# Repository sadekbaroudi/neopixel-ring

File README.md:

# fingerpunch neopixel ring

Two rings, seprated by breakaway tabs (mouse bites)

You can use it as one large ring, or break them apart for two smaller rings

## fabrication

This is set up to use at JLCPCB. You can fab with PCBA.

All the necessary files are in the pcb/production directory in this repository.

## images

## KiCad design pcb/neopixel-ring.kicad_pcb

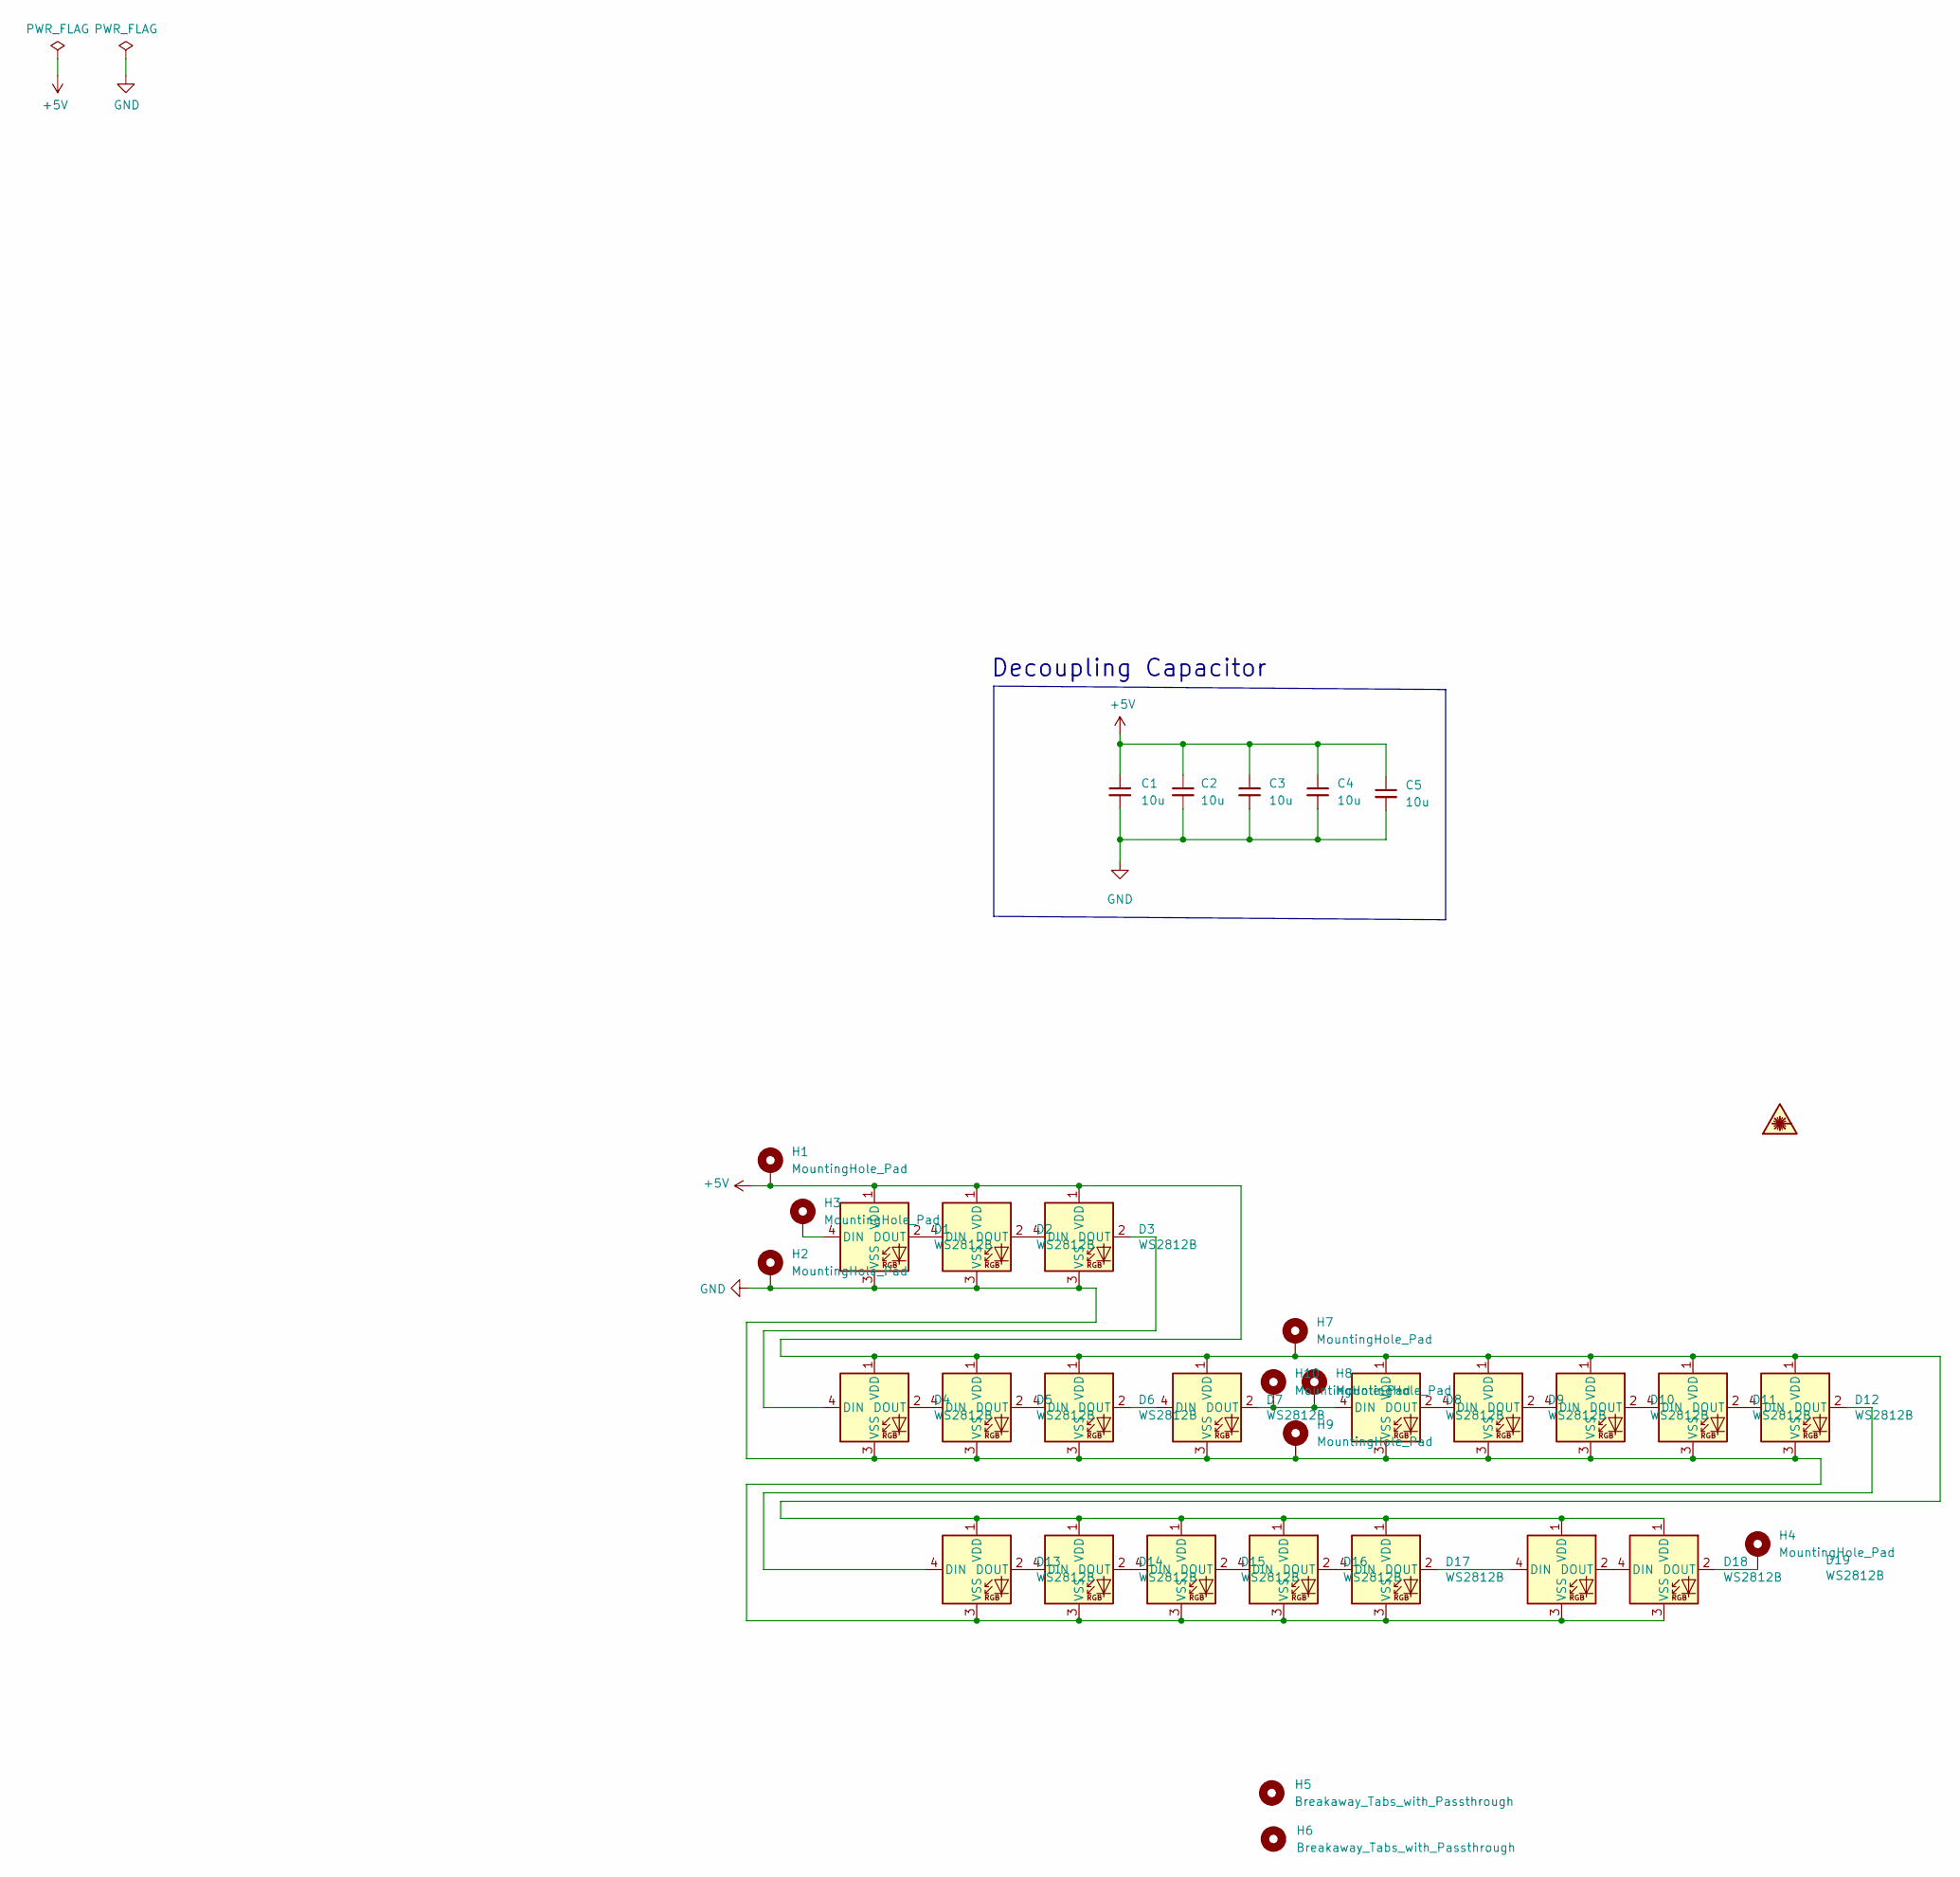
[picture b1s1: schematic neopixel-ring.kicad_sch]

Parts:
C1, C2, C3, C4, C5: 10u; C_0402_1005Metric; LCSC C2846677
D1, D2, D3, D4, D5, D6, D7, D8, D9, D10, D11, D12, D13, D14, D15, D16, D17, D18, D19: WS2812B; MPN WS2812B-B/W; LCSC C2761795
H1, H2, H3, H4, H7, H8, H9, H10: MountingHole_Pad; Pin_D0.7mm_L6.5mm_W1.8mm_FlatFork
H5, H6: Breakaway_Tabs_with_Passthrough

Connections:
+5V: C1.1, C2.1, C3.1, C4.1, C5.1, D1.1 (VDD), D2.1 (VDD), D3.1 (VDD), D4.1 (VDD), D5.1 (VDD), D6.1 (VDD), D7.1 (VDD), D8.1 (VDD), D9.1 (VDD), D10.1 (VDD), D11.1 (VDD), D12.1 (VDD), D13.1 (VDD), D14.1 (VDD), D15.1 (VDD), D16.1 (VDD), D17.1 (VDD), D18.1 (VDD), D19.1 (VDD), H1.1, H7.1
GND: C1.2, C2.2, C3.2, C4.2, C5.2, D1.3 (VSS), D2.3 (VSS), D3.3 (VSS), D4.3 (VSS), D5.3 (VSS), D6.3 (VSS), D7.3 (VSS), D8.3 (VSS), D9.3 (VSS), D10.3 (VSS), D11.3 (VSS), D12.3 (VSS), D13.3 (VSS), D14.3 (VSS), D15.3 (VSS), D16.3 (VSS), D17.3 (VSS), D18.3 (VSS), D19.3 (VSS), H2.1, H9.1
unnamed: D1.2 (DOUT), D2.4 (DIN)
unnamed: D1.4 (DIN), H3.1
unnamed: D2.2 (DOUT), D3.4 (DIN)
unnamed: D4.2 (DOUT), D5.4 (DIN)
unnamed: D3.2 (DOUT), D4.4 (DIN)
unnamed: D5.2 (DOUT), D6.4 (DIN)
unnamed: D7.2 (DOUT), D8.4 (DIN), H8.1, H10.1
unnamed: D6.2 (DOUT), D7.4 (DIN)
unnamed: D8.2 (DOUT), D9.4 (DIN)
unnamed: D9.2 (DOUT), D10.4 (DIN)
unnamed: D10.2 (DOUT), D11.4 (DIN)
unnamed: D11.2 (DOUT), D12.4 (DIN)
unnamed: D12.2 (DOUT), D13.4 (DIN)
unnamed: D13.2 (DOUT), D14.4 (DIN)
unnamed: D14.2 (DOUT), D15.4 (DIN)
unnamed: D15.2 (DOUT), D16.4 (DIN)
unnamed: D16.2 (DOUT), D17.4 (DIN)
unnamed: D18.2 (DOUT), D19.4 (DIN)
unnamed: D17.2 (DOUT), D18.4 (DIN)
unnamed: D19.2 (DOUT), H4.1

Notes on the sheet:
Decoupling Capacitor

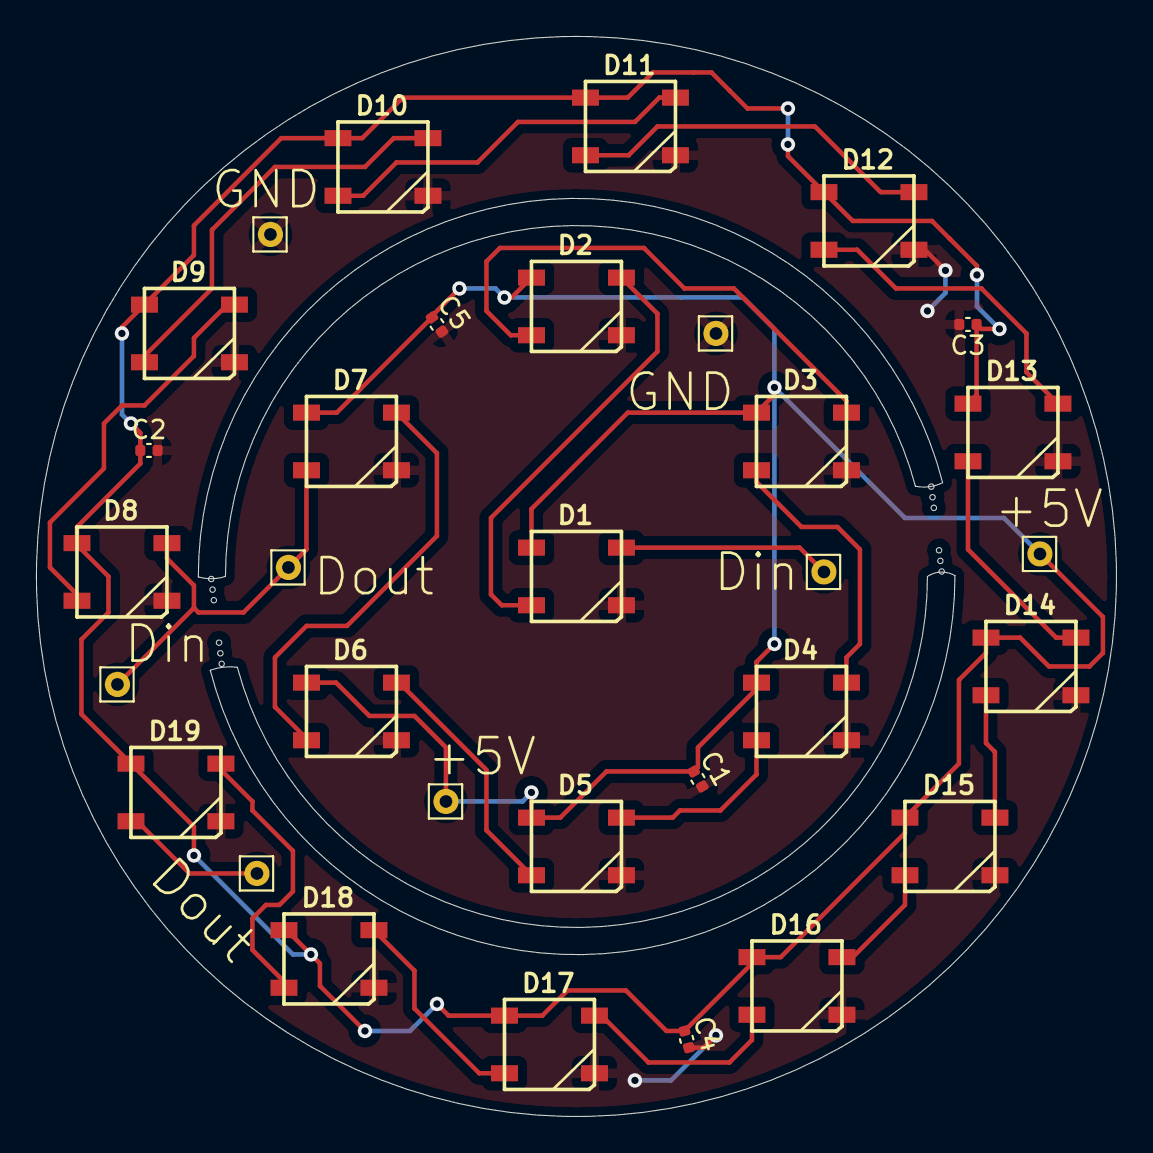
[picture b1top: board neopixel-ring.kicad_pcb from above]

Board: 2 copper layers, 60.0 x 60.0 mm, 34 parts (0 on the bottom side), 22 nets.

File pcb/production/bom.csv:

Designator,Footprint,Quantity,Value,LCSC Part #
"C1, C2, C3, C4, C5",C_0402_1005Metric,5,10u,C2846677
"D1, D10, D11, D12, D13, D14, D15, D16, D17, D18, D19, D2, D3, D4, D5, D6, D7, D8, D9",WS2812B,19,WS2812B,C2761795
"H1, H10, H2, H3, H4, H7, H8, H9",Pin_D0.7mm_L6.5mm_W1.8mm_FlatFork,8,MountingHole_Pad,
"H5, H6",Breakaway_Tabs_with_Passthrough,2,Breakaway_Tabs_with_Passthrough,

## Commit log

2022-12-28 first revision of neopixel ring
